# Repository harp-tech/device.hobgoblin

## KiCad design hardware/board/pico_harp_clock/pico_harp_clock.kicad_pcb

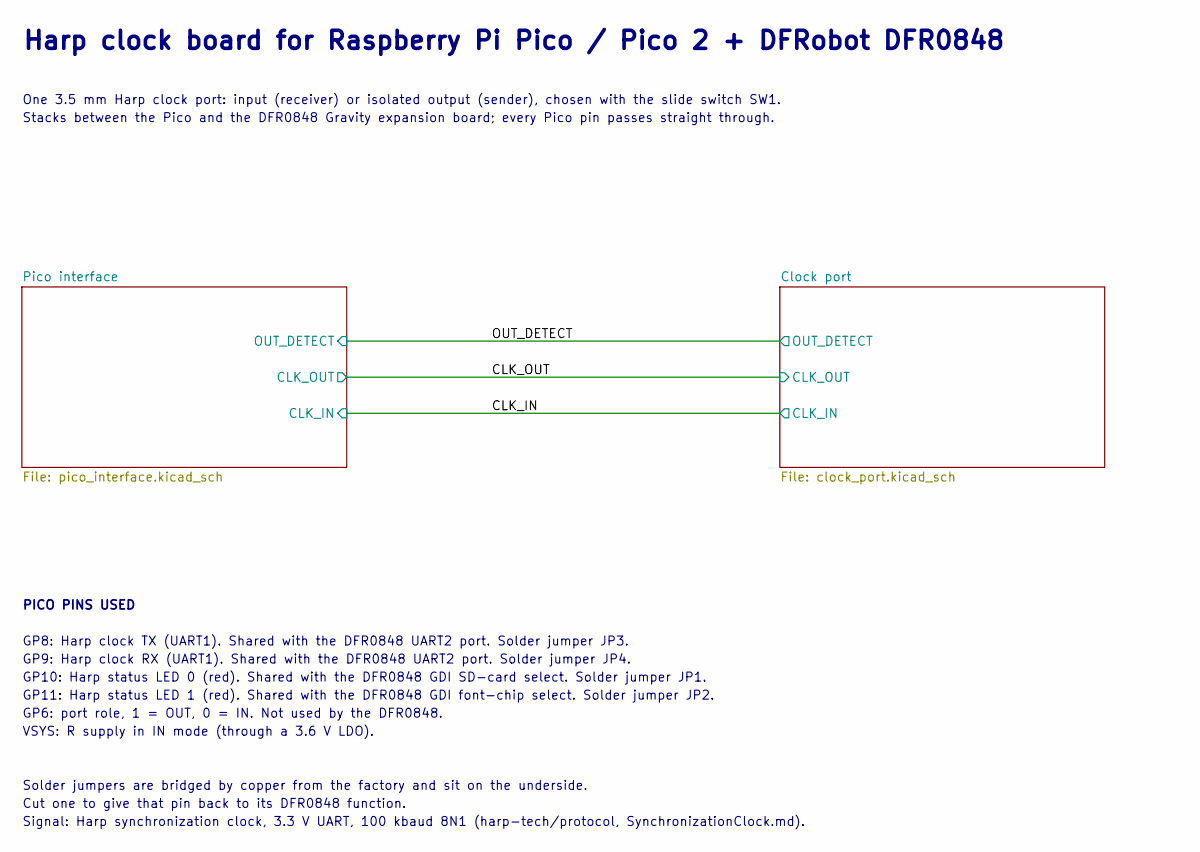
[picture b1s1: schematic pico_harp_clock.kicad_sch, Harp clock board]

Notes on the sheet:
Harp clock board for Raspberry Pi Pico / Pico 2 + DFRobot DFR0848
One 3.5 mm Harp clock port: input (receiver) or isolated output (sender), chosen with the slide switch SW1.
Stacks between the Pico and the DFR0848 Gravity expansion board; every Pico pin passes straight through.
PICO PINS USED
GP8: Harp clock TX (UART1). Shared with the DFR0848 UART2 port. Solder jumper JP3.
GP9: Harp clock RX (UART1). Shared with the DFR0848 UART2 port. Solder jumper JP4.
GP10: Harp status LED 0 (red). Shared with the DFR0848 GDI SD-card select. Solder jumper JP1.
GP11: Harp status LED 1 (red). Shared with the DFR0848 GDI font-chip select. Solder jumper JP2.
GP6: port role, 1 = OUT, 0 = IN. Not used by the DFR0848.
VSYS: R supply in IN mode (through a 3.6 V LDO).
Solder jumpers are bridged by copper from the factory and sit on the underside.
Cut one to give that pin back to its DFR0848 function.
Signal: Harp synchronization clock, 3.3 V UART, 100 kbaud 8N1 (harp-tech/protocol, SynchronizationClock.md).

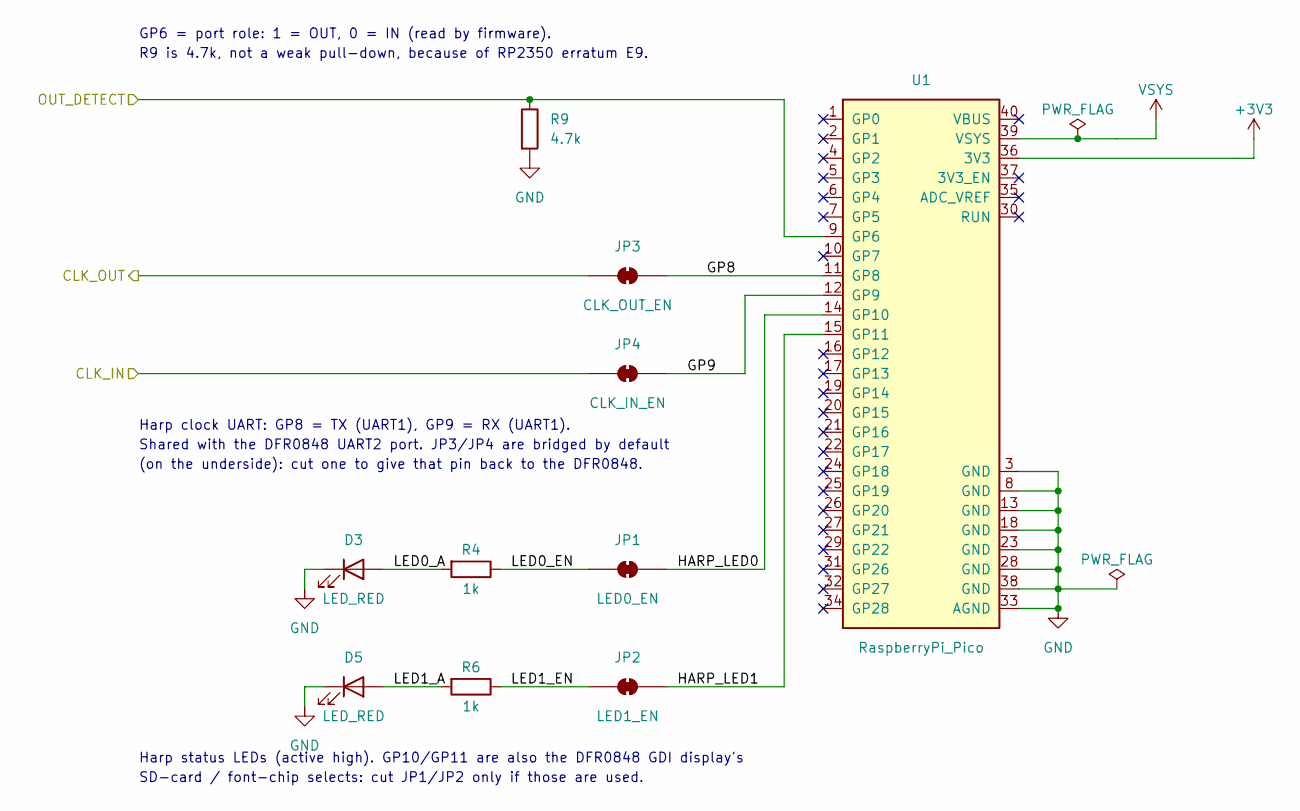
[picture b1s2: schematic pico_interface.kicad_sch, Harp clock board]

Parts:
D3, D5: LED_RED; LED_0603_1608Metric; MPN KT-0603R; LCSC C2286
JP1: LED0_EN; SolderJumper-2_P1.3mm_Bridged_RoundedPad1.0x1.5mm
JP2: LED1_EN; SolderJumper-2_P1.3mm_Bridged_RoundedPad1.0x1.5mm
JP3: CLK_OUT_EN; SolderJumper-2_P1.3mm_Bridged_RoundedPad1.0x1.5mm
JP4: CLK_IN_EN; SolderJumper-2_P1.3mm_Bridged_RoundedPad1.0x1.5mm
R4, R6: 1k; R_0603_1608Metric; MPN 0603WAF1001T5E; LCSC C21190
R9: 4.7k; R_0603_1608Metric; MPN 0603WAF4701T5E; LCSC C23162
U1: RaspberryPi_Pico; RaspberryPi_Pico_Common_THT

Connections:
+3V3: U1.36 (3V3); also elsewhere on the board
/CLK_IN: JP4.2 (B); also elsewhere on the board
/CLK_OUT: JP3.2 (B); also elsewhere on the board
/OUT_DETECT: R9.1, U1.9 (GP6); also elsewhere on the board
/Pico interface/GP8: JP3.1 (A), U1.11 (GP8)
/Pico interface/GP9: JP4.1 (A), U1.12 (GP9)
/Pico interface/HARP_LED0: JP1.1 (A), U1.14 (GP10)
/Pico interface/HARP_LED1: JP2.1 (A), U1.15 (GP11)
/Pico interface/LED0_A: D3.2 (A), R4.2
/Pico interface/LED0_EN: JP1.2 (B), R4.1
/Pico interface/LED1_A: D5.2 (A), R6.2
/Pico interface/LED1_EN: JP2.2 (B), R6.1
GND: D3.1 (K), D5.1 (K), R9.2, U1.3 (GND), U1.8 (GND), U1.13 (GND), U1.18 (GND), U1.23 (GND), U1.28 (GND), U1.33 (AGND), U1.38 (GND); also elsewhere on the board
VSYS: U1.39 (VSYS); also elsewhere on the board

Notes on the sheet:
GP6 = port role: 1 = OUT, 0 = IN (read by firmware).
R9 is 4.7k, not a weak pull-down, because of RP2350 erratum E9.
Harp clock UART: GP8 = TX (UART1), GP9 = RX (UART1).
Shared with the DFR0848 UART2 port. JP3/JP4 are bridged by default
(on the underside): cut one to give that pin back to the DFR0848.
Harp status LEDs (active high). GP10/GP11 are also the DFR0848 GDI display's
SD-card / font-chip selects: cut JP1/JP2 only if those are used.

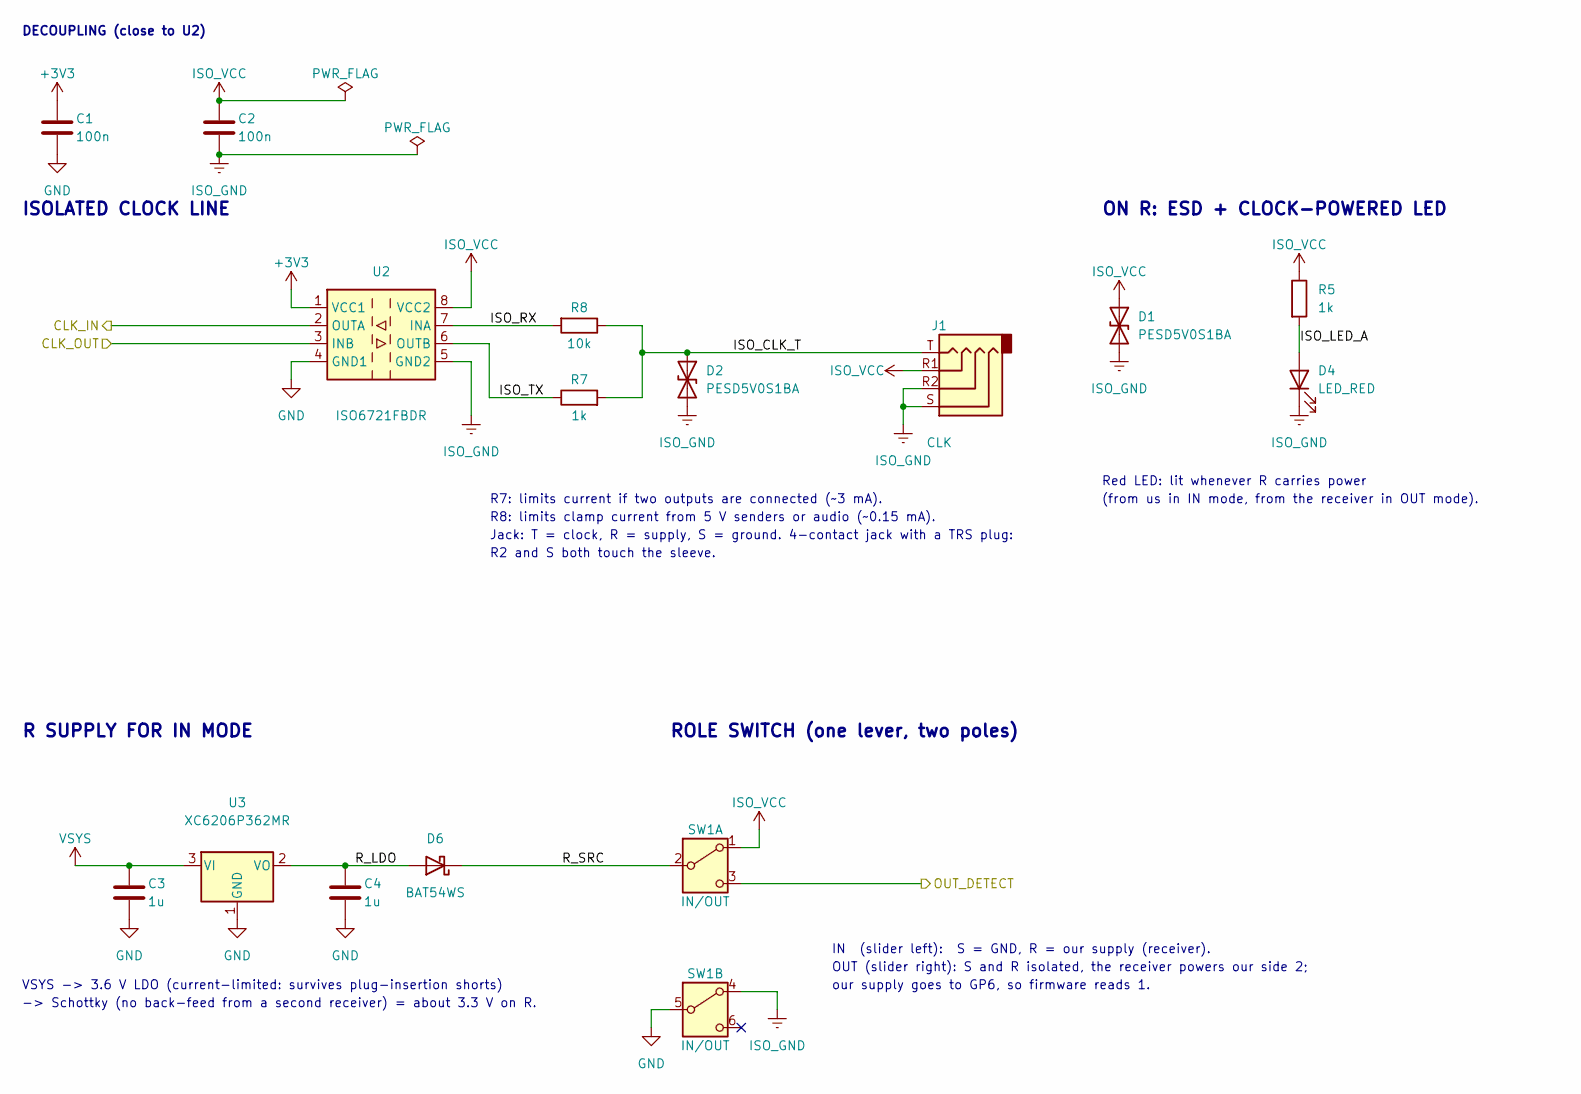
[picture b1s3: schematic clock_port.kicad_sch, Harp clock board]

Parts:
C1, C2: 100n; C_0603_1608Metric; MPN CC0603KRX7R9BB104; LCSC C14663
C3, C4: 1u; C_0603_1608Metric; MPN CL10A105KB8NNNC; LCSC C15849
D1, D2: PESD5V0S1BA; D_SOD-323; MPN PESD5V0S1BA,115; LCSC C19224
D4: LED_RED; LED_0603_1608Metric; MPN KT-0603R; LCSC C2286
D6: BAT54WS; D_SOD-323; MPN BAT54WS-7-F; LCSC C124205
J1: CLK; Jack_3.5mm_KoreanHropartsElec_PJ-320D-4A_Horizontal; MPN PJ-320D-4A; LCSC C95562
R5, R7: 1k; R_0603_1608Metric; MPN 0603WAF1001T5E; LCSC C21190
R8: 10k; R_0603_1608Metric; MPN 0603WAF1002T5E; LCSC C25804
SW1: IN/OUT; SW_DPDT_CK_JS202011JCQN; MPN JS202011JCQN; LCSC C221665
U2: ISO6721FBDR; SOIC-8_3.9x4.9mm_P1.27mm; MPN ISO6721FBDR; LCSC C5216431
U3: XC6206P362MR; SOT-23-3; MPN XC6206P362MR; LCSC C351446

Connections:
+3V3: C1.1, U2.1 (VCC1); also elsewhere on the board
/CLK_IN: U2.2 (OUTA); also elsewhere on the board
/CLK_OUT: U2.3 (INB); also elsewhere on the board
/Clock port/ISO_CLK_T: D2.1 (A1), J1.T, R7.2, R8.1
/Clock port/ISO_LED_A: D4.2 (A), R5.2
/Clock port/ISO_RX: R8.2, U2.7 (INA)
/Clock port/ISO_TX: R7.1, U2.6 (OUTB)
/Clock port/R_LDO: C4.1, D6.2 (A), U3.2 (VO)
/Clock port/R_SRC: D6.1 (K), SW1.2 (B)
/OUT_DETECT: SW1.3 (C); also elsewhere on the board
GND: C1.2, C3.2, C4.2, SW1.5 (B), U2.4 (GND1), U3.1 (GND); also elsewhere on the board
ISO_GND: C2.2, D1.2 (A2), D2.2 (A2), D4.1 (K), J1.R2, J1.S, SW1.4 (A), U2.5 (GND2)
ISO_VCC: C2.1, D1.1 (A1), J1.R1, R5.1, SW1.1 (A), U2.8 (VCC2)
VSYS: C3.1, U3.3 (VI); also elsewhere on the board

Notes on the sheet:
ISOLATED CLOCK LINE
R7: limits current if two outputs are connected (~3 mA).
R8: limits clamp current from 5 V senders or audio (~0.15 mA).
Jack: T = clock, R = supply, S = ground. 4-contact jack with a TRS plug:
R2 and S both touch the sleeve.
DECOUPLING (close to U2)
ON R: ESD + CLOCK-POWERED LED
Red LED: lit whenever R carries power
(from us in IN mode, from the receiver in OUT mode).
R SUPPLY FOR IN MODE
VSYS -> 3.6 V LDO (current-limited: survives plug-insertion shorts)
-> Schottky (no back-feed from a second receiver) = about 3.3 V on R.
ROLE SWITCH (one lever, two poles)
IN (slider left): S = GND, R = our supply (receiver).
OUT (slider right): S and R isolated, the receiver powers our side 2;
our supply goes to GP6, so firmware reads 1.

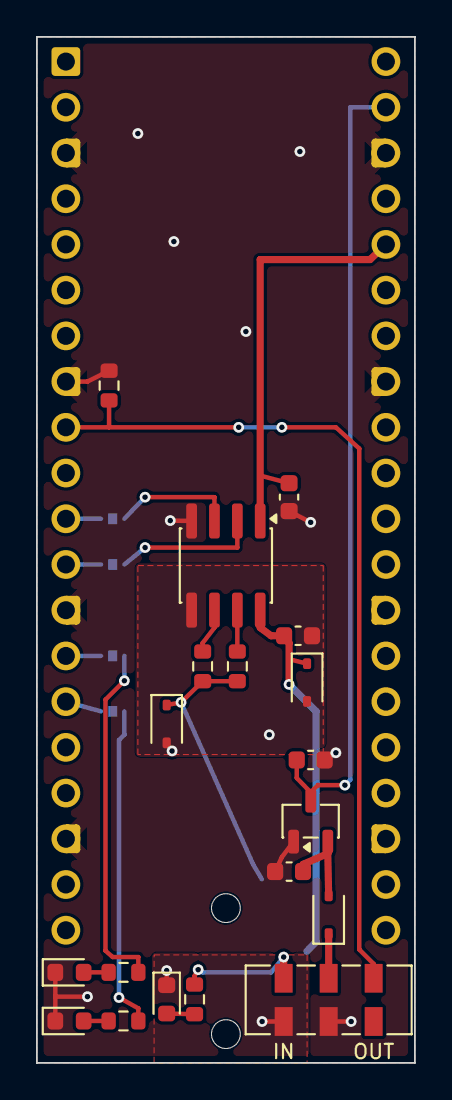
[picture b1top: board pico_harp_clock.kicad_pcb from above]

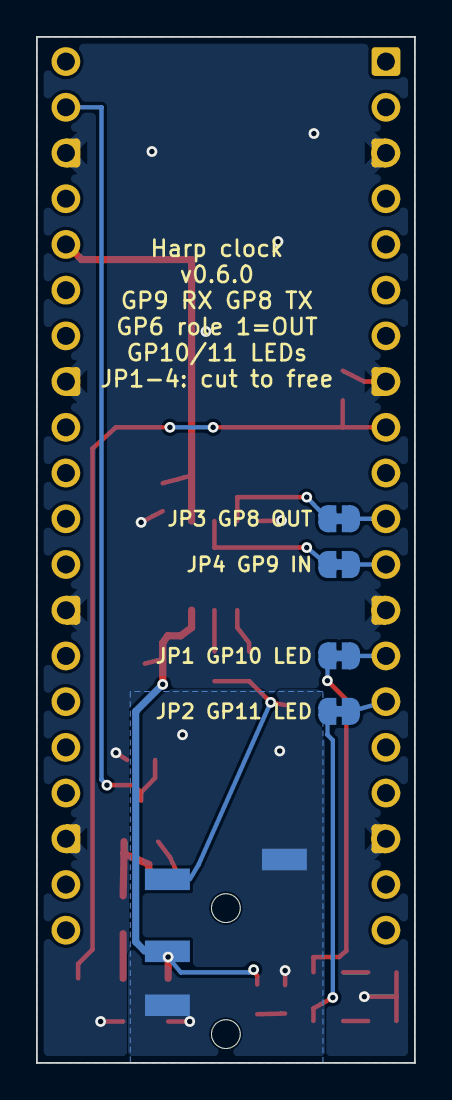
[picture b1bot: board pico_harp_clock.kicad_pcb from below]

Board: 2 copper layers, 21.0 x 57.0 mm, 25 parts (5 on the bottom side), 22 nets.
